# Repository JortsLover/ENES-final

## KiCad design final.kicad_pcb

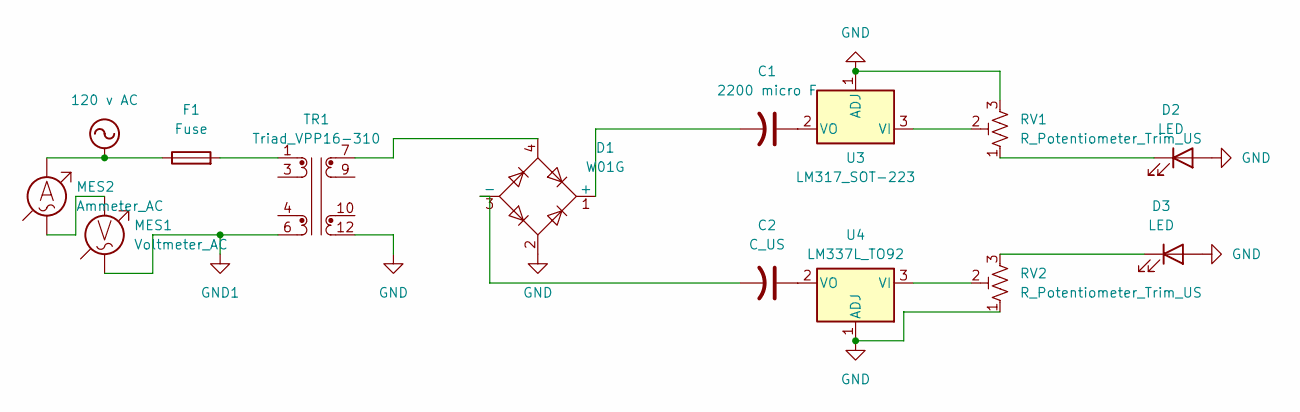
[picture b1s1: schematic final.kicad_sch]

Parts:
C1: 2200 micro F; CP_Radial_D10.0mm_P5.00mm
C2: C_US; CP_Radial_D10.0mm_P5.00mm
D1: W01G; Diode_Bridge_Round_D9.8mm
D2, D3: LED; LED-APA102-2020
F1: Fuse; Fuseholder_Littelfuse_Nano2_154x
MES1: Voltmeter_AC; TerminalBlock_Altech_AK300-2_P5.00mm
MES2: Ammeter_AC; TerminalBlock_Altech_AK300-2_P5.00mm
RV1, RV2: R_Potentiometer_Trim_US; Potentiometer_Bourns_3296W_Vertical
TR1: Triad_VPP16-310; Transformer_Triad_VPP16-310
U3: LM317_SOT-223; SOT-223-3_TabPin2
U4: LM337L_TO92; TO-92_Inline

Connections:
120 v AC: F1.1, MES2.2
GND: D1.2, D2.2 (A), D3.2 (A), RV1.3, RV2.1, TR1.12, U3.1 (ADJ), U4.1 (ADJ)
GND1: MES1.1, TR1.6
unnamed: C1.2, D1.1 (+)
unnamed: C2.2, D1.3 (-)
unnamed: D1.4, TR1.7
unnamed: D2.1 (K), RV1.1
unnamed: D3.1 (K), RV2.3
unnamed: F1.2, TR1.1
unnamed: MES1.2, MES2.1
unnamed: RV1.2, U3.3 (VI)
unnamed: C1.1, U3.2 (VO)
unnamed: RV2.2, U4.3 (VI)
unnamed: C2.1, U4.2 (VO)

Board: 2 copper layers, 13 parts (0 on the bottom side), 14 nets, no tracks yet.
